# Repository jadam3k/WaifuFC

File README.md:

# Flight Controller Project

This repository contains the final design of a **flight controller**, including the BOM, schematic, PCB layout, and 3D model preview.  
This design uses a **4-layer PCB** for stable power distribution and signal integrity.  
---

## Bill of Materials (BOM)

Below is the list of essential components used in the flight controller. These are the components required for proper operation:

| Designator(s)              | Quantity       | Component Name / Description                                |
|-----------------------------|---------------|-------------------------------------------------------------|
| C1, C10, C14, C2, C3, C4, C5, C9 | JLCPCB PCBA | 100nF 0402 Ceramic Capacitor                                 |
| C11                        | JLCPCB PCBA   | 2.2nF 0402 Ceramic Capacitor                                |
| C12                        | JLCPCB PCBA   | 10uF/50V 1206 Ceramic Capacitor                              |
| C13                        | JLCPCB PCBA   | 150pF 0402 Ceramic Capacitor                                  |
| C15                        | JLCPCB PCBA   | 22uF/16V 1206 Ceramic Capacitor                               |
| C16, C17                   | JLCPCB PCBA   | 10uF 0805 Ceramic Capacitor                                   |
| C6, C7                     | JLCPCB PCBA   | 20pF 0402 Ceramic Capacitor                                   |
| C8                         | JLCPCB PCBA   | 10nF 0402 Ceramic Capacitor                                   |
| D1, D2                     | JLCPCB PCBA   | SS34 Schottky Diode                                           |
| D3, D5                     | JLCPCB PCBA   | Red LED 0603                                                 |
| D4                         | JLCPCB PCBA   | Blue LED 0603                                                |
| D6                         | JLCPCB PCBA   | S7 Diode SOD-123                                             |
| J1                         | JLCPCB PCBA   | 3-pin Header Pad (SBUS)                                      |
| J2                         | 11 PLN   | USB-C Receptacle, Palconn UTC16-G, USB2.0                    |
| J3                         | JLCPCB PCBA   | 3-pin Header Pad (PPM)                                       |
| J4                         | JLCPCB PCBA   | 6-pin Header Pad (OUT)                                       |
| J5, J6                     | JLCPCB PCBA   | 2-pin Connector Pad                                          |
| J7                         | JLCPCB PCBA   | 4-pin Connector Pad                                          |
| L1                         | JLCPCB PCBA   | 15uH / 3A Power Inductor, SMD Neosid SM-PIC0602H            |
| NT1                        | JLCPCB PCBA   | Net Tie, 2 pads SMD 2.0mm                                   |
| Q1                         | JLCPCB PCBA   | 1P NPN Transistor, SOT-23, MMBT2222A                        |
| R1, R2                     | JLCPCB PCBA   | 10kΩ 0402 Resistor                                           |
| R10                        | JLCPCB PCBA   | 24kΩ 0402 Resistor                                           |
| R11, R12, R18, R9          | JLCPCB PCBA   | 100kΩ 0402 Resistor                                          |
| R13                        | JLCPCB PCBA   | 200kΩ 0402 Resistor                                          |
| R14                        | JLCPCB PCBA   | 39kΩ 0402 Resistor                                           |
| R15                        | JLCPCB PCBA   | 150Ω 0402 Resistor                                           |
| R16                        | JLCPCB PCBA   | 330Ω 0402 Resistor                                           |
| R17                        | JLCPCB PCBA   | 260Ω 0402 Resistor                                           |
| R19                        | JLCPCB PCBA   | 12kΩ 0402 Resistor                                           |
| R20, R21                   | JLCPCB PCBA   | 5.1kΩ 0402 Resistor                                          |
| R3, R4, R5, R6             | JLCPCB PCBA   | 4.7kΩ 0402 Resistor                                          |
| R7, R8                     | JLCPCB PCBA   | 22Ω 0402 Resistor                                            |
| SW1                        | JLCPCB PCBA   | SPST Push Button Switch B3U-1000P                            |
| U1                         | JLCPCB PCBA   | STM32F103C8T6 Microcontroller, LQFP-48, 7x7mm               |
| U2                         | JLCPCB PCBA   | MPU-6050 3-axis Gyroscope & Accelerometer, QFN-24 4x4mm      |
| U3                         | JLCPCB PCBA   | MP1584 Buck Converter, SOIC-8                                  |
| U4                         | JLCPCB PCBA   | AZ1117-3.3V Voltage Regulator, SOT-89-3                       |
| Y1                         | JLCPCB PCBA   | 8MHz Crystal Oscillator, SMD 3225 4-pin                      |

> The BOM above is based on the `bom.csv` file in the repository.  

---

## Schematic

---

## PCB Layout and 3D Preview

---

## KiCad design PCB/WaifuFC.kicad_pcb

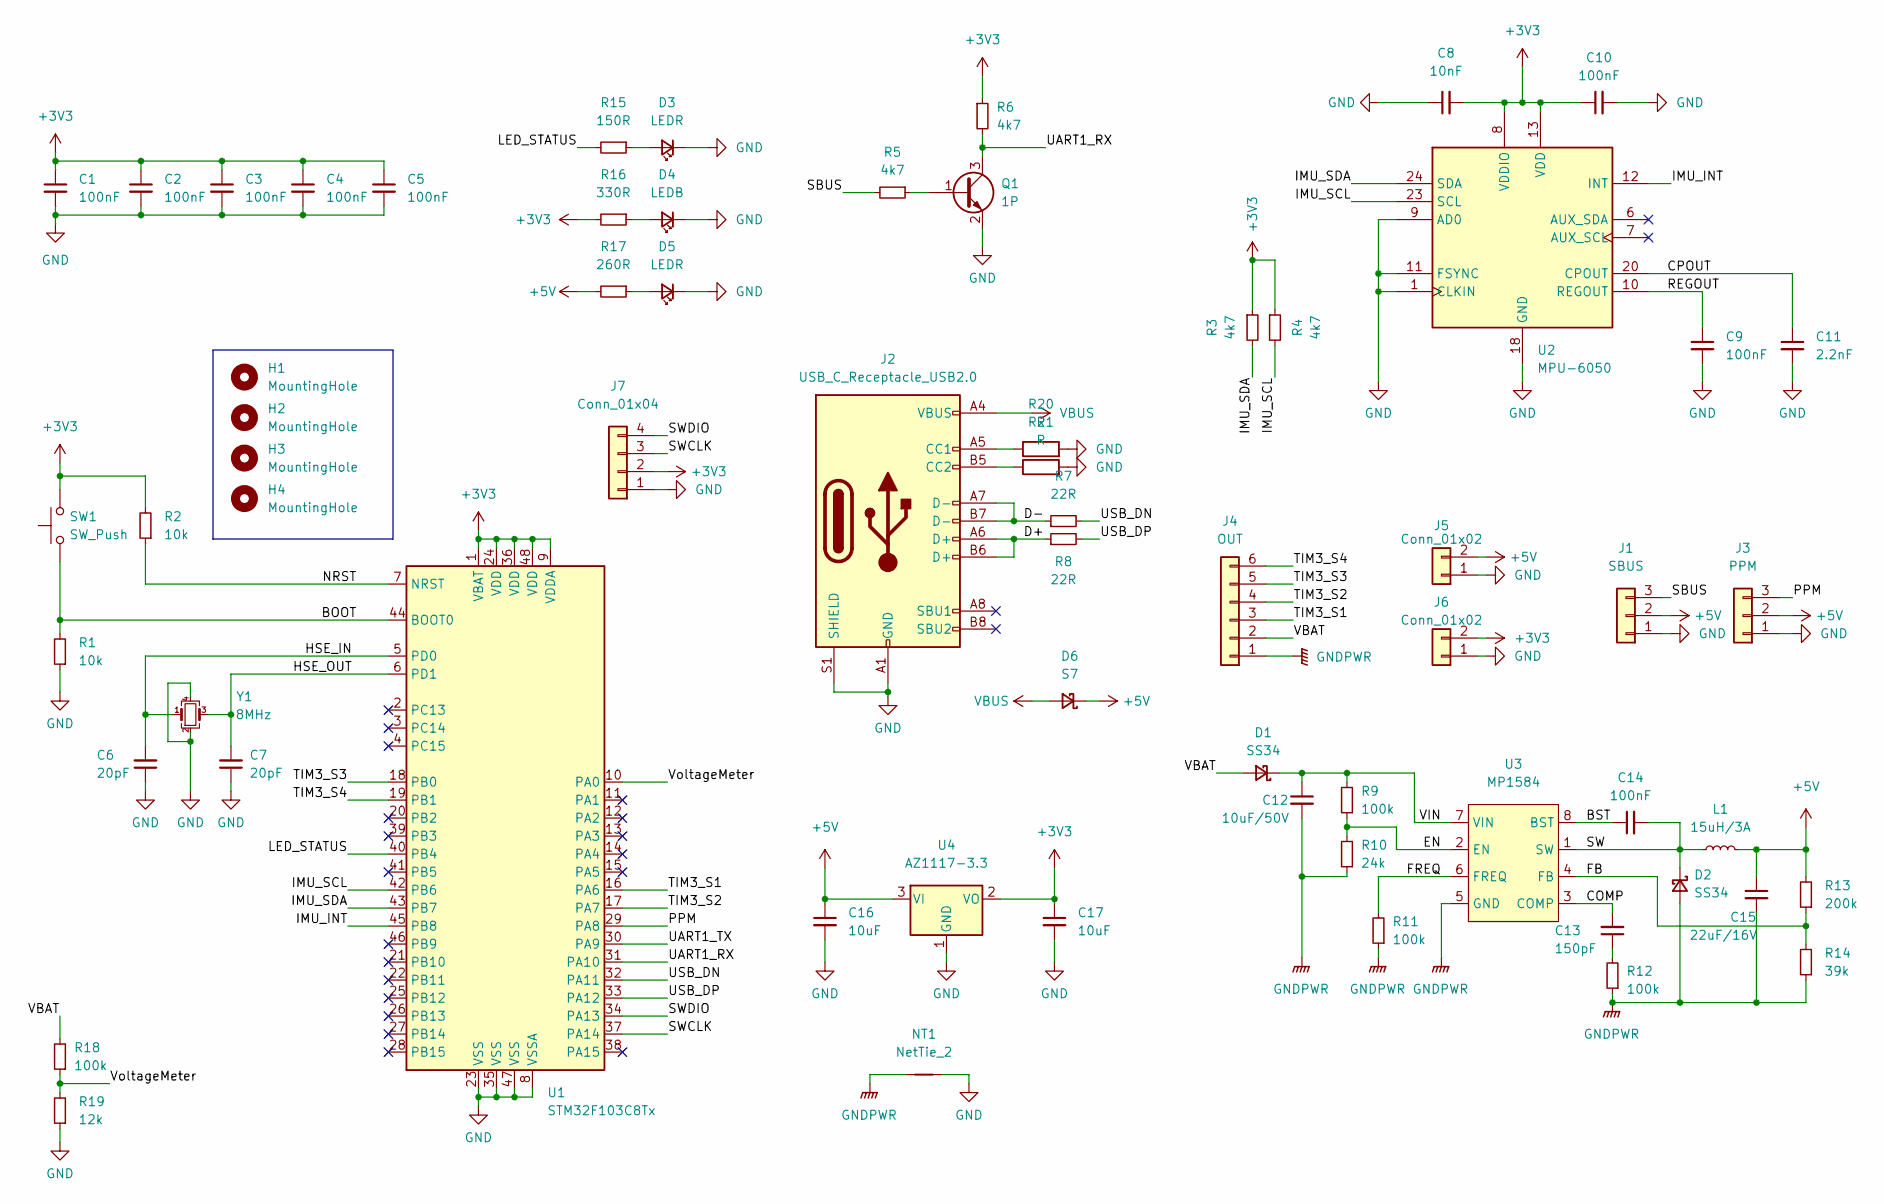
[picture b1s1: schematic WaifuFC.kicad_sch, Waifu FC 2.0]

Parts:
C1, C2, C3, C4, C5, C9, C10, C14: 100nF; C_0402_1005Metric
C6, C7: 20pF; C_0402_1005Metric
C8: 10nF; C_0402_1005Metric
C11: 2.2nF; C_0402_1005Metric
C12: 10uF/50V; C_1206_3216Metric
C13: 150pF; C_0402_1005Metric
C15: 22uF/16V; C_1206_3216Metric
C16, C17: 10uF; C_0805_2012Metric
D1, D2: SS34; D_SMA
D3, D5: LEDR; LED_0603_1608Metric
D4: LEDB; LED_0603_1608Metric
D6: S7; D_SOD-123
H1, H2, H3, H4: MountingHole; MountingHole_3mm_Pad
J1: SBUS; pad_01x03
J2: USB_C_Receptacle_USB2.0; USB_C_Receptacle_Palconn_UTC16-G
J3: PPM; pad_01x03
J4: OUT; pad_01x06
J5, J6: Conn_01x02; pad_01x02
J7: Conn_01x04; pad_01x04
L1: 15uH/3A; L_Neosid_SM-PIC0602H
NT1: NetTie_2; NetTie-2_SMD_Pad2.0mm
Q1: 1P; SOT-23
R1, R2: 10k; R_0402_1005Metric
R3, R4, R5, R6: 4k7; R_0402_1005Metric
R7, R8: 22R; R_0402_1005Metric
R9, R11, R12, R18: 100k; R_0402_1005Metric
R10: 24k; R_0402_1005Metric
R13: 200k; R_0402_1005Metric
R14: 39k; R_0402_1005Metric
R15: 150R; R_0402_1005Metric
R16: 330R; R_0402_1005Metric
R17: 260R; R_0402_1005Metric
R19: 12k; R_0402_1005Metric
R20, R21: R; R_0402_1005Metric
SW1: SW_Push; SW_SPST_B3U-1000P
U1: STM32F103C8Tx; LQFP-48_7x7mm_P0.5mm
U2: MPU-6050; InvenSense_QFN-24_4x4mm_P0.5mm
U3: MP1584; SOIC-8-1EP_3.9x4.9mm_P1.27mm_EP2.29x3mm_ThermalVias
U4: AZ1117-3.3; SOT-89-3
Y1: 8MHz; Crystal_SMD_3225-4Pin_3.2x2.5mm

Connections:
+3V3: C1.1, C2.1, C3.1, C4.1, C5.1, C8.2, C10.1, C17.1, J6.2, J7.2, R2.2, R3.1, R4.1, R6.1, R16.2, SW1.2, U1.1 (VBAT), U1.9 (VDDA), U1.24 (VDD), U1.36 (VDD), U1.48 (VDD), U2.8 (VDDIO), U2.13 (VDD), U4.2 (VO)
+5V: C15.1, C16.1, D6.1 (K), J1.2, J3.2, J5.2, L1.2, R13.2, R17.2, U4.3 (VI)
/BOOT: R1.2, SW1.1, U1.44 (BOOT0)
/BST: C14.1, U3.8 (BST)
/COMP: C13.2, U3.3 (COMP)
/CPOUT: C11.1, U2.20 (CPOUT)
/D+: J2.A6 (D+), J2.B6 (D+), R8.1
/D-: J2.A7 (D-), J2.B7 (D-), R7.1
/EN: R9.1, R10.2, U3.2 (EN)
/FB: R13.1, R14.2, U3.4 (FB)
/FREQ: R11.2, U3.6 (FREQ)
/HSE_IN: C6.2, U1.5 (PD0), Y1.1
/HSE_OUT: C7.2, U1.6 (PD1), Y1.3
/IMU_INT: U1.45 (PB8), U2.12 (INT)
/IMU_SCL: R4.2, U1.42 (PB6), U2.23 (SCL)
/IMU_SDA: R3.2, U1.43 (PB7), U2.24 (SDA)
/LED_STATUS: R15.2, U1.40 (PB4)
/NRST: R2.1, U1.7 (NRST)
/PPM: J3.3, U1.29 (PA8)
/REGOUT: C9.1, U2.10 (REGOUT)
/SBUS: J1.3, R5.2
/SW: C14.2, D2.1 (K), L1.1, U3.1 (SW)
/SWCLK: J7.3, U1.37 (PA14)
/SWDIO: J7.4, U1.34 (PA13)
/TIM3_S1: J4.3, U1.16 (PA6)
/TIM3_S2: J4.4, U1.17 (PA7)
/TIM3_S3: J4.5, U1.18 (PB0)
/TIM3_S4: J4.6, U1.19 (PB1)
/UART1_RX: Q1.3 (C), R6.2, U1.31 (PA10)
/UART1_TX: U1.30 (PA9)
/USB_DN: R7.2, U1.32 (PA11)
/USB_DP: R8.2, U1.33 (PA12)
/VBAT: D1.2 (A), J4.2, R18.2
/VIN: C12.1, D1.1 (K), R9.2, U3.7 (VIN)
/VoltageMeter: R18.1, R19.2, U1.10 (PA0)
GND: C1.2, C2.2, C3.2, C4.2, C5.2, C6.1, C7.1, C8.1, C9.2, C10.2, C11.2, C16.2, C17.2, D3.1 (K), D4.1 (K), D5.1 (K), J1.1, J2.A1 (GND), J2.A12 (GND), J2.B1 (GND), J2.B12 (GND), J2.S1 (SHIELD), J3.1, J5.1, J6.1, J7.1, NT1.2, Q1.2 (E), R1.1, R19.1, R20.2, R21.2, U1.8 (VSSA), U1.23 (VSS), U1.35 (VSS), U1.47 (VSS), U2.1 (CLKIN), U2.9 (AD0), U2.11 (FSYNC), U2.18 (GND), U4.1 (GND), Y1.2, Y1.4
GNDPWR: C12.2, C15.2, D2.2 (A), J4.1, NT1.1, R10.1, R11.1, R12.1, R14.1, U3.5 (GND)
unnamed: C13.1, R12.2
unnamed: D3.2 (A), R15.1
unnamed: D4.2 (A), R16.1
unnamed: D5.2 (A), R17.1
unnamed: J2.A5 (CC1), R20.1
unnamed: J2.B5 (CC2), R21.1
unnamed: Q1.1 (B), R5.1
VBUS: D6.2 (A), J2.A4 (VBUS), J2.A9 (VBUS), J2.B4 (VBUS), J2.B9 (VBUS)

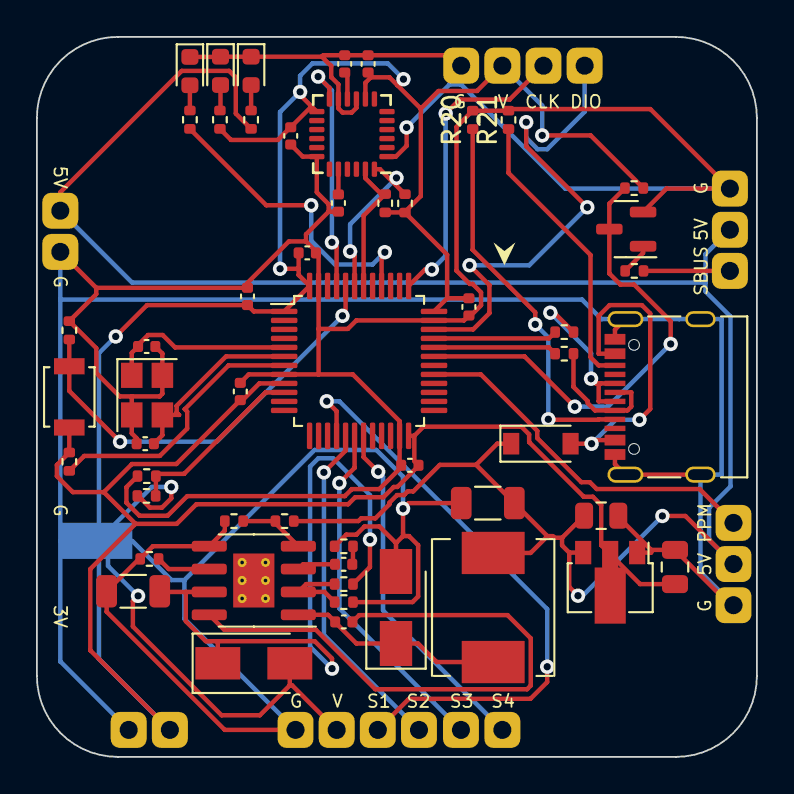
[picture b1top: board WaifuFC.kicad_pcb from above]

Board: 2 copper layers, 40.0 x 40.0 mm, 60 parts (1 on the bottom side), 44 nets.

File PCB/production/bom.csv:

Designator,Footprint,Quantity,Value,LCSC Part #
"C1, C10, C14, C2, C3, C4, C5, C9",0402,8,100nF,
C11,0402,1,2.2nF,
C12,1206,1,10uF/50V,
C13,0402,1,150pF,
C15,1206,1,22uF/16V,
"C16, C17",0805,2,10uF,
"C6, C7",0402,2,20pF,
C8,0402,1,10nF,
"D1, D2",D_SMA,2,SS34,
"D3, D5",0603,2,LEDR,
D4,0603,1,LEDB,
D6,D_SOD-123,1,S7,
J1,pad_01x03,1,SBUS,
J2,USB_C_Receptacle_Palconn_UTC16-G,1,USB_C_Receptacle_USB2.0,
J3,pad_01x03,1,PPM,
J4,pad_01x06,1,OUT,
"J5, J6",pad_01x02,2,Conn_01x02,
J7,pad_01x04,1,Conn_01x04,
L1,L_Neosid_SM-PIC0602H,1,15uH/3A,
NT1,NetTie-2_SMD_Pad2.0mm,1,NetTie_2,
Q1,SOT-23,1,1P,
"R1, R2",0402,2,10k,
R10,0402,1,24k,
"R11, R12, R18, R9",0402,4,100k,
R13,0402,1,200k,
R14,0402,1,39k,
R15,0402,1,150R,
R16,0402,1,330R,
R17,0402,1,260R,
R19,0402,1,12k,
"R3, R4, R5, R6",0402,4,4k7,
"R7, R8",0402,2,22R,
SW1,SW_SPST_B3U-1000P,1,SW_Push,
U1,LQFP-48_7x7mm_P0.5mm,1,STM32F103C8Tx,
U2,InvenSense_QFN-24_4x4mm_P0.5mm,1,MPU-6050,
U3,SOIC-8-1EP_3.9x4.9mm_P1.27mm_EP2.29x3mm_ThermalVias,1,MP1584,
U4,SOT-89-3,1,AZ1117-3.3,
Y1,Crystal_SMD_3225-4Pin_3.2x2.5mm,1,8MHz,

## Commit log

2025-11-24 elo2
2025-11-25 fixes
2025-12-02 elowina
2025-12-27 Update Bill of Materials with additional components
    Expanded the Bill of Materials (BOM) section with additional components and their quantities, specifying that they are sourced from JLCPCB PCBA.
2025-12-27 Enhance BOM with component descriptions
    Updated the Bill of Materials (BOM) section to include component descriptions.
2025-12-27 Modify USB-C Receptacle entry in bom.csv
    Updated price for USB-C Receptacle in BOM.
2025-12-27 Revise BOM with designators and pricing
    Updated BOM to include component designators and prices.
